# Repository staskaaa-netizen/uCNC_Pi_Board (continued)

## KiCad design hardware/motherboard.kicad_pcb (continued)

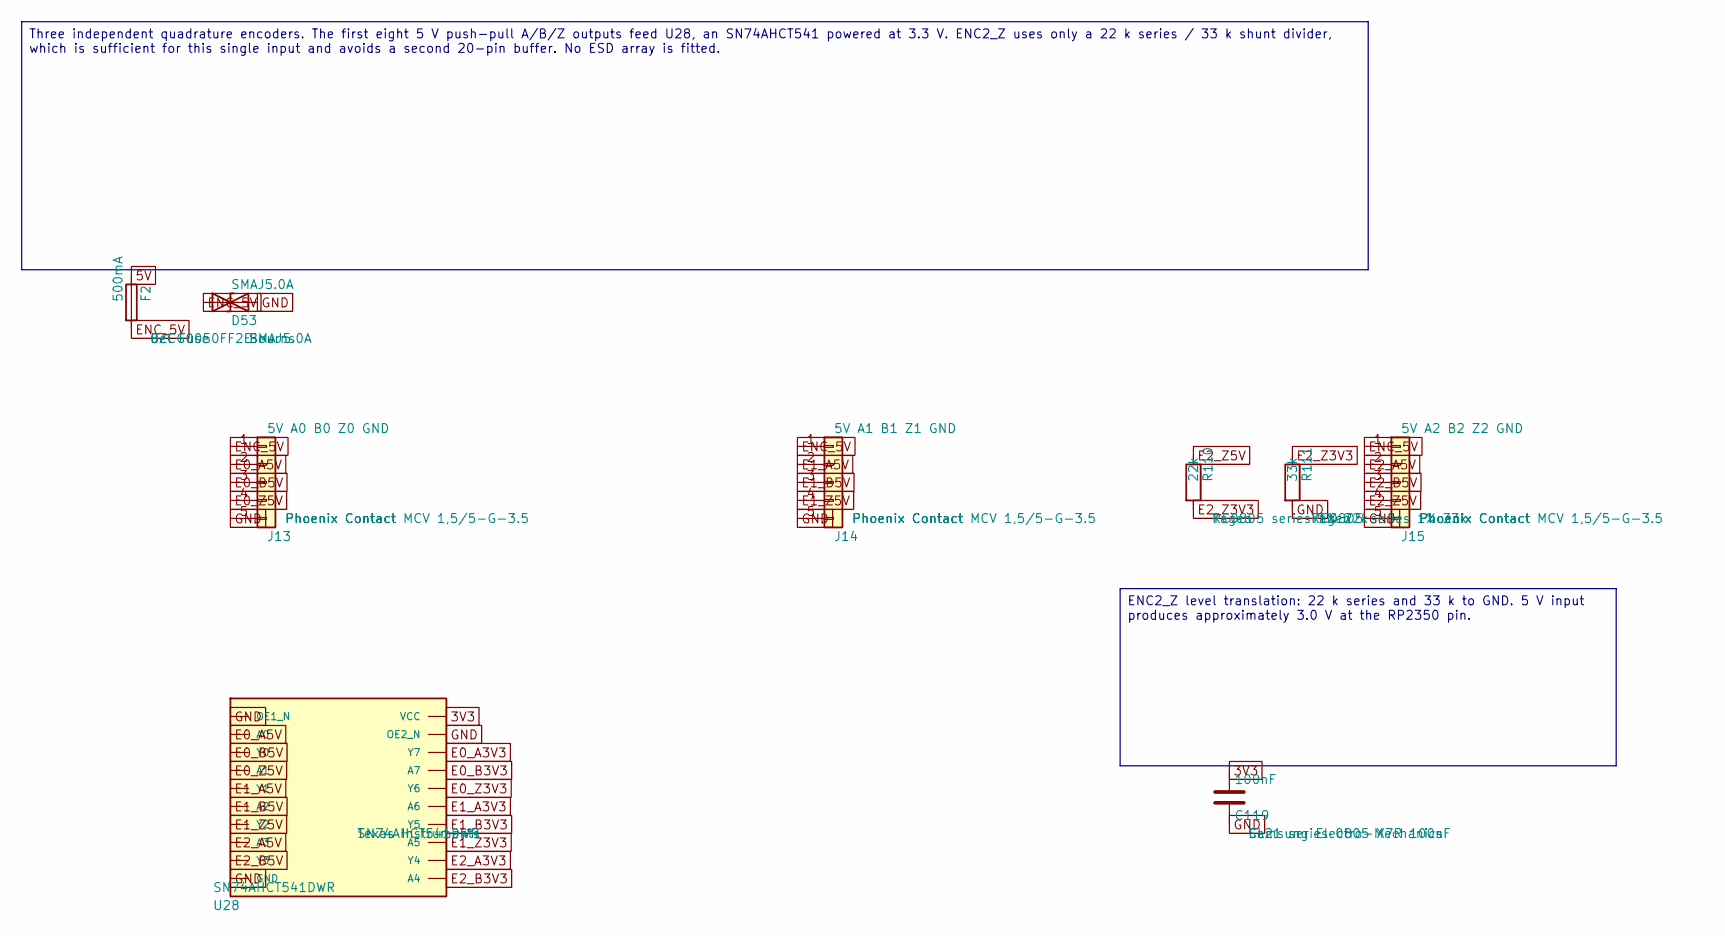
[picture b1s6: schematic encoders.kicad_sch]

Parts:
C119: 100nF; C_0805_2012Metric; MPN CL21 series 0805 X7R 100nF
D53: SMAJ5.0A; D_SMA; MPN SMAJ5.0A
F2: 500mA; R_1206_3216Metric; MPN 0ZCG0050FF2E
J13: 5V A0 B0 Z0 GND; PhoenixContact_MCV_1,5_5-G-3.5_1x05_P3.50mm_Vertical; MPN Phoenix Contact MCV 1,5/5-G-3.5
J14: 5V A1 B1 Z1 GND; PhoenixContact_MCV_1,5_5-G-3.5_1x05_P3.50mm_Vertical; MPN Phoenix Contact MCV 1,5/5-G-3.5
J15: 5V A2 B2 Z2 GND; PhoenixContact_MCV_1,5_5-G-3.5_1x05_P3.50mm_Vertical; MPN Phoenix Contact MCV 1,5/5-G-3.5
R110: 22k; R_0805_2012Metric; MPN RC0805 series 1% 22k
R111: 33k; R_0805_2012Metric; MPN RC0805 series 1% 33k
U28: SN74AHCT541DWR; SOIC-20W_7.5x12.8mm_P1.27mm; MPN SN74AHCT541DWR

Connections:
3V3: C119.1, U28.20 (VCC); also elsewhere on the board
5V: F2.1; also elsewhere on the board
E0_A3V3: U28.18 (Y7); also elsewhere on the board
E0_A5V: J13.2, U28.2 (A0)
E0_B3V3: U28.17 (A7); also elsewhere on the board
E0_B5V: J13.3, U28.3 (Y0)
E0_Z3V3: U28.16 (Y6); also elsewhere on the board
E0_Z5V: J13.4, U28.4 (A1)
E1_A3V3: U28.15 (A6); also elsewhere on the board
E1_A5V: J14.2, U28.5 (Y1)
E1_B3V3: U28.14 (Y5); also elsewhere on the board
E1_B5V: J14.3, U28.6 (A2)
E1_Z3V3: U28.13 (A5); also elsewhere on the board
E1_Z5V: J14.4, U28.7 (Y2)
E2_A3V3: U28.12 (Y4); also elsewhere on the board
E2_A5V: J15.2, U28.8 (A3)
E2_B3V3: U28.11 (A4); also elsewhere on the board
E2_B5V: J15.3, U28.9 (Y3)
E2_Z3V3: R110.2, R111.1; also elsewhere on the board
E2_Z5V: J15.4, R110.1
ENC_5V: D53.1 (A1), F2.2, J13.1, J14.1, J15.1
GND: C119.2, D53.2 (A2), J13.5, J14.5, J15.5, R111.2, U28.1 (OE1_N), U28.10 (GND), U28.19 (OE2_N); also elsewhere on the board

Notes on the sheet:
Three independent quadrature encoders. The first eight 5 V push-pull A/B/Z outputs feed U28, an SN74AHCT541 powered at 3.3 V. ENC2_Z uses only a 22 k series / 33 k shunt divider, which is sufficient for this single input and avoids a second 20-pin buffer. No ESD array is fitted.
ENC2_Z level translation: 22 k series and 33 k to GND. 5 V input produces approximately 3.0 V at the RP2350 pin.

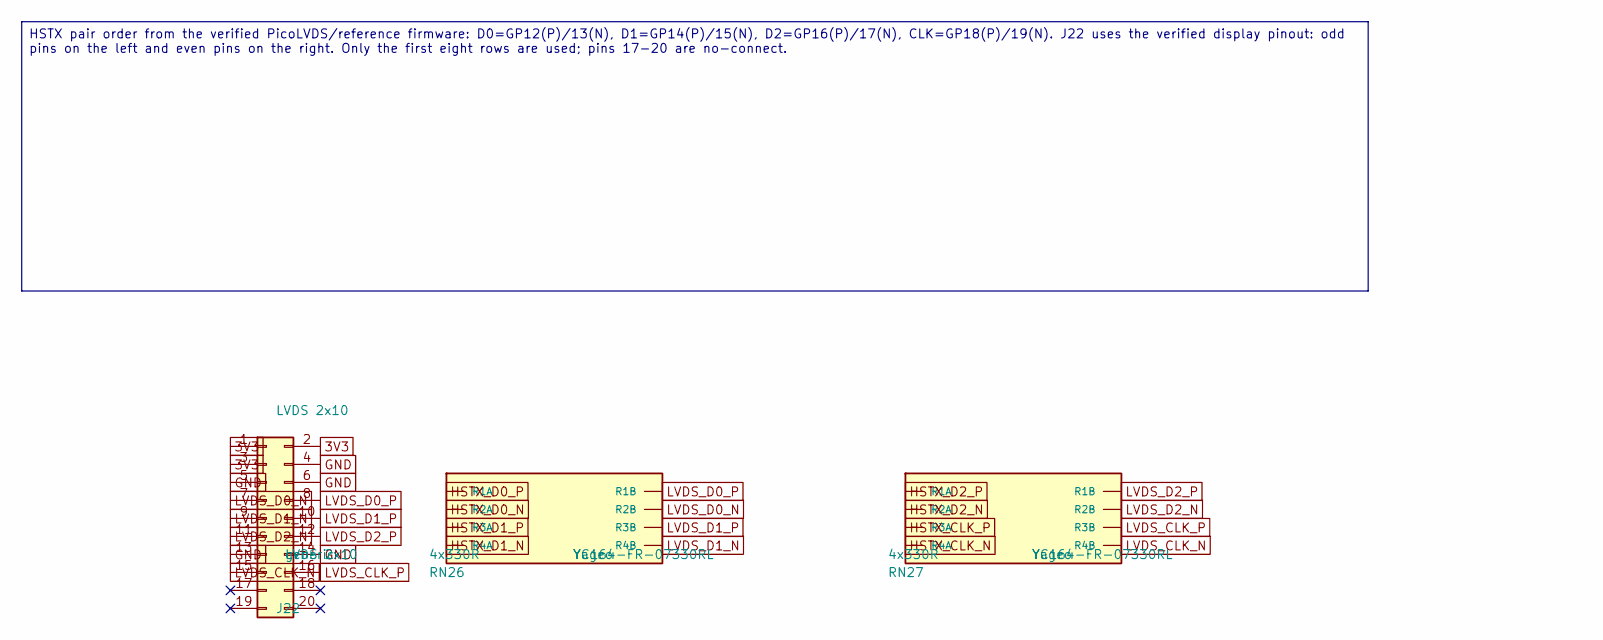
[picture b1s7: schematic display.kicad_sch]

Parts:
J22: LVDS 2x10; PinHeader_2x10_P2.00mm_Vertical; MPN LVDS 2x10
RN26, RN27: 4x330R; R_Array_Convex_4x0603; MPN YC164-FR-07330RL

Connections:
3V3: J22.1, J22.2, J22.3; also elsewhere on the board
GND: J22.4, J22.5, J22.6, J22.13, J22.14; also elsewhere on the board
HSTX_CLK_N: RN27.4 (R4A); also elsewhere on the board
HSTX_CLK_P: RN27.3 (R3A); also elsewhere on the board
HSTX_D0_N: RN26.2 (R2A); also elsewhere on the board
HSTX_D0_P: RN26.1 (R1A); also elsewhere on the board
HSTX_D1_N: RN26.4 (R4A); also elsewhere on the board
HSTX_D1_P: RN26.3 (R3A); also elsewhere on the board
HSTX_D2_N: RN27.2 (R2A); also elsewhere on the board
HSTX_D2_P: RN27.1 (R1A); also elsewhere on the board
LVDS_CLK_N: J22.15, RN27.5 (R4B)
LVDS_CLK_P: J22.16, RN27.6 (R3B)
LVDS_D0_N: J22.7, RN26.7 (R2B)
LVDS_D0_P: J22.8, RN26.8 (R1B)
LVDS_D1_N: J22.9, RN26.5 (R4B)
LVDS_D1_P: J22.10, RN26.6 (R3B)
LVDS_D2_N: J22.11, RN27.7 (R2B)
LVDS_D2_P: J22.12, RN27.8 (R1B)

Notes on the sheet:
HSTX pair order from the verified PicoLVDS/reference firmware: D0=GP12(P)/13(N), D1=GP14(P)/15(N), D2=GP16(P)/17(N), CLK=GP18(P)/19(N). J22 uses the verified display pinout: odd pins on the left and even pins on the right. Only the first eight rows are used; pins 17-20 are no-connect.

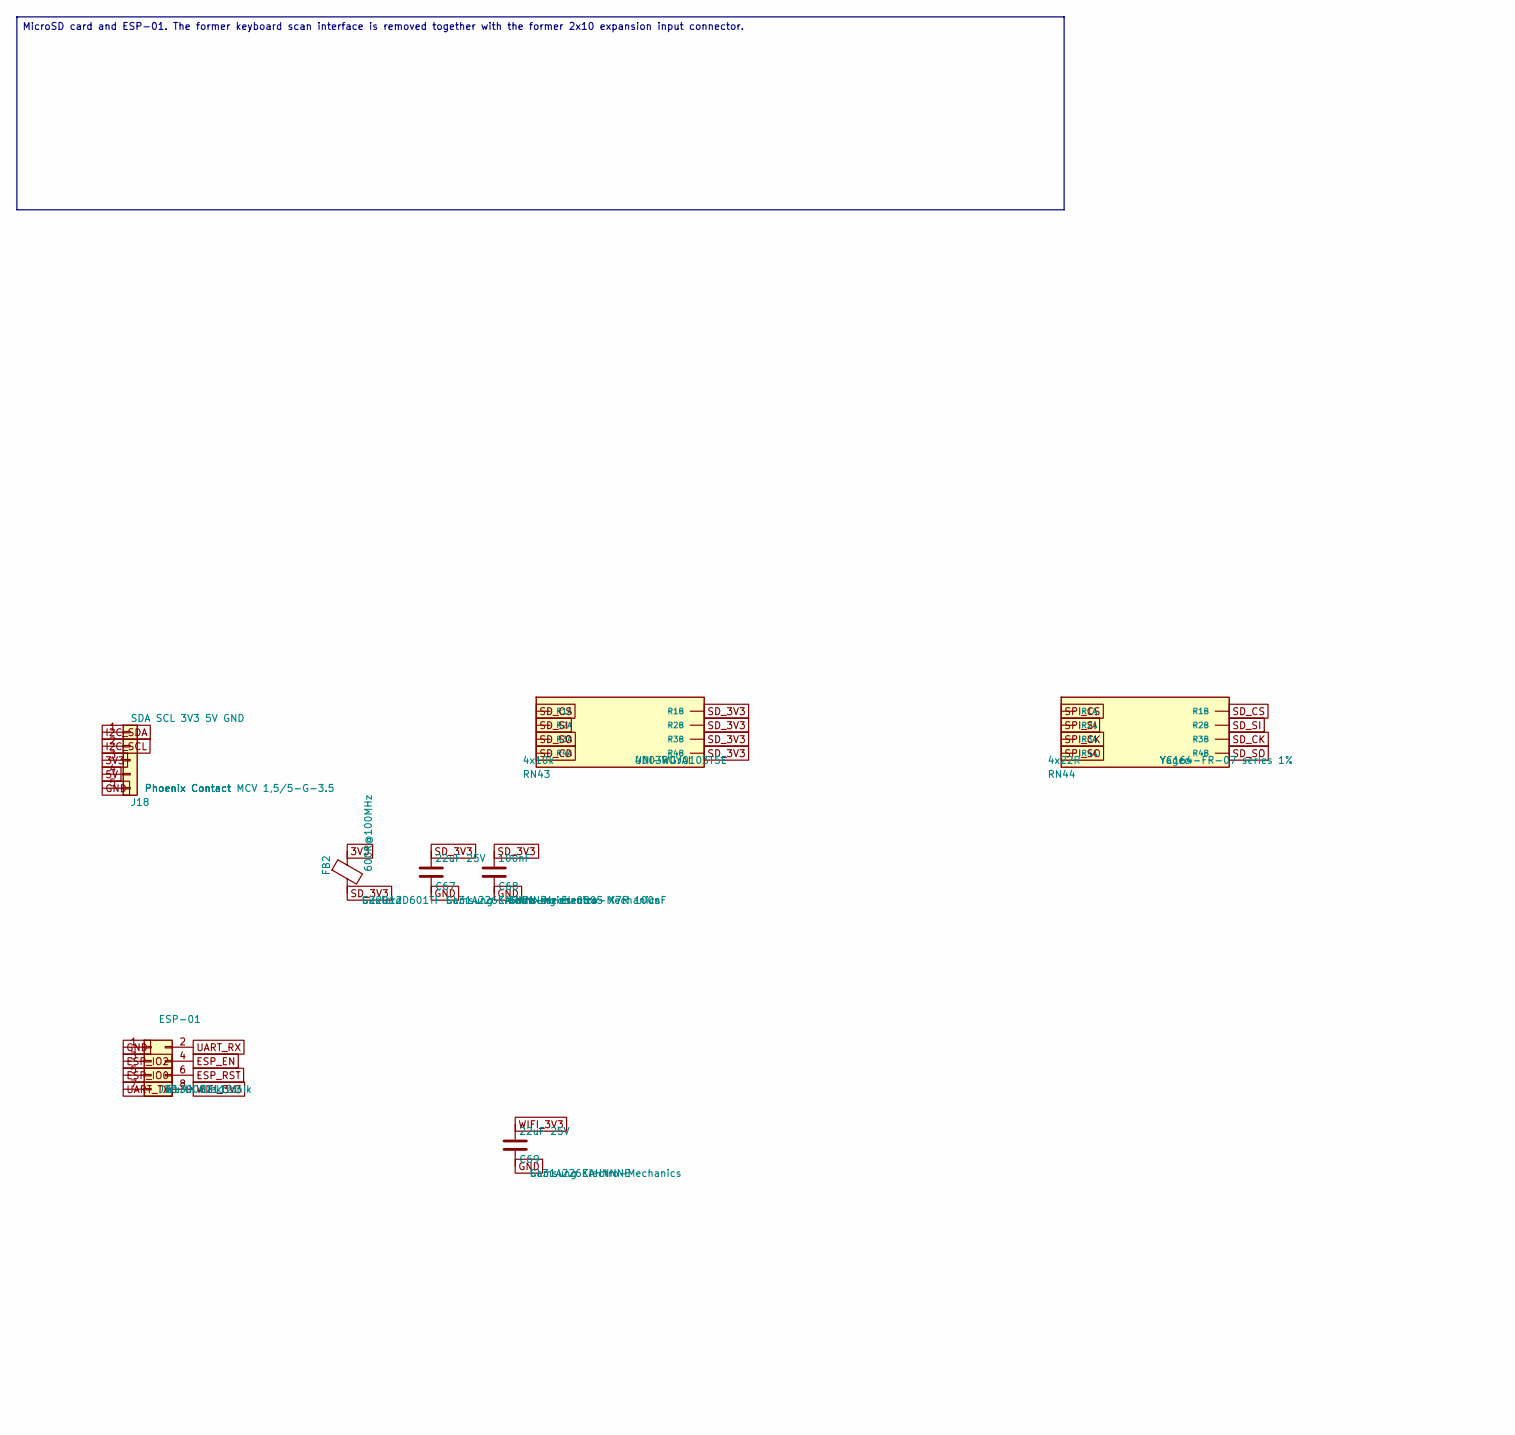
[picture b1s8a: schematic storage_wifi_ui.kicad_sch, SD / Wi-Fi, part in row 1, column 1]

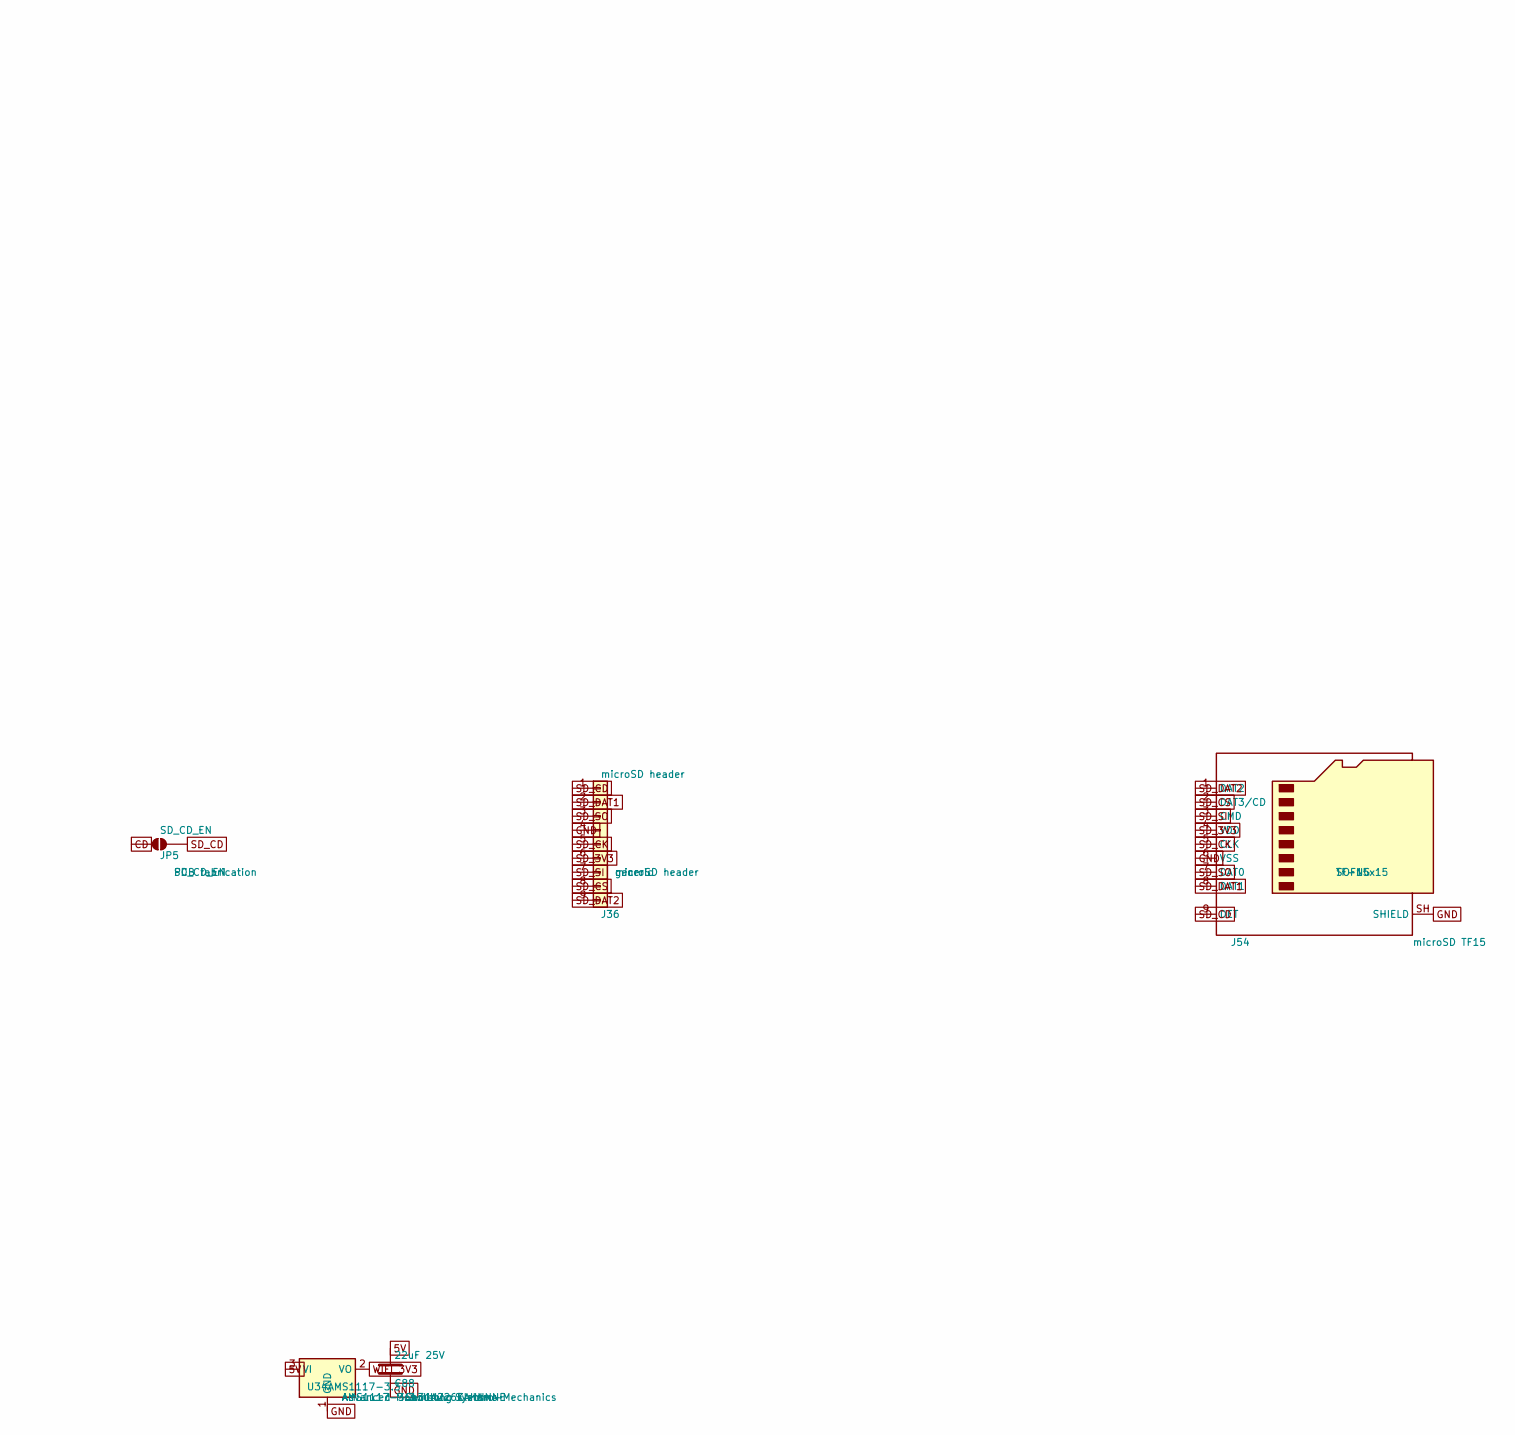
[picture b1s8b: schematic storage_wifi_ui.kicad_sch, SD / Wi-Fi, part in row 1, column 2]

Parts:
C67, C69, C88: 22uF 25V; C_1206_3216Metric; MPN CL31A226KAHNNNE
C68: 100nF; C_0805_2012Metric; MPN CL21 series 0805 X7R 100nF
FB2: 600R@100MHz; R_0805_2012Metric; MPN GZ2012D601TF
J18: SDA SCL 3V3 5V GND; PhoenixContact_MCV_1,5_5-G-3.5_1x05_P3.50mm_Vertical; MPN Phoenix Contact MCV 1,5/5-G-3.5
J20: ESP-01; PinSocket_2x04_P2.54mm_Vertical; MPN 61300821121
J36: microSD header; PinHeader_1x09_P2.54mm_Vertical; MPN microSD header
J54: microSD TF15; TF-SMD_TF-15-15; MPN TF-15x15
JP5: SD_CD_EN; SolderJumper-2_P1.3mm_Open_Pad1.0x1.5mm; MPN SD_CD_EN
RN43: 4x10k; R_Array_Convex_4x0603; MPN 4D03WGJ0103T5E
RN44: 4x22R; R_Array_Convex_4x0603; MPN YC164-FR-07 series 1%
U34: AMS1117-3.3; SOT-223-3_TabPin2; MPN AMS1117-3.3

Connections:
3V3: FB2.1, J18.3; also elsewhere on the board
5V: C88.1, J18.4, U34.3 (VI); also elsewhere on the board
CD: JP5.1 (A); also elsewhere on the board
ESP_EN: J20.4
ESP_IO0: J20.5
ESP_IO2: J20.3
ESP_RST: J20.6
GND: C67.2, C68.2, C69.2, C88.2, J18.5, J20.1, J36.4, J54.6 (VSS), J54.10, J54.11, J54.12, J54.13, J54.SH (SHIELD), U34.1 (GND); also elsewhere on the board
I2C_SCL: J18.2; also elsewhere on the board
I2C_SDA: J18.1; also elsewhere on the board
SD_3V3: C67.1, C68.1, FB2.2, J36.6, J54.4 (VDD), RN43.5 (R4B), RN43.6 (R3B), RN43.7 (R2B), RN43.8 (R1B)
SD_CD: J36.1, J54.9 (DET), JP5.2 (B), RN43.4 (R4A)
SD_CK: J36.5, J54.5 (CLK), RN44.6 (R3B)
SD_CS: J36.8, J54.2 (DAT3/CD), RN43.1 (R1A), RN44.8 (R1B)
SD_DAT1: J36.2, J54.8 (DAT1)
SD_DAT2: J36.9, J54.1 (DAT2)
SD_SI: J36.7, J54.3 (CMD), RN43.2 (R2A), RN44.7 (R2B)
SD_SO: J36.3, J54.7 (DAT0), RN43.3 (R3A), RN44.5 (R4B)
SPI_CK: RN44.3 (R3A); also elsewhere on the board
SPI_CS: RN44.1 (R1A); also elsewhere on the board
SPI_SI: RN44.2 (R2A); also elsewhere on the board
SPI_SO: RN44.4 (R4A); also elsewhere on the board
UART_RX: J20.2; also elsewhere on the board
UART_TX: J20.7; also elsewhere on the board
WIFI_3V3: C69.1, J20.8, U34.2 (VO)

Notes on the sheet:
MicroSD card and ESP-01. The former keyboard scan interface is removed together with the former 2x10 expansion input connector.

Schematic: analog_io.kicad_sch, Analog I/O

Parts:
C73, C74, C75, C93, C95, C97, C99, C102, C118: 100nF; C_0805_2012Metric; MPN CL21 series 0805 X7R 100nF
C92, C94, C96, C98: 1uF; C_0805_2012Metric; MPN CL21 series 0805 X7R 1uF
C100: 22uF 35V; C_1210_3225Metric; MPN CL32 series 1210 X7R 22uF 35V
C101: 22uF 25V; C_1206_3216Metric; MPN CL31A226KAHNNNE
J24: GND AI0 AI1 AI2 AI3; PhoenixContact_MCV_1,5_5-G-3.5_1x05_P3.50mm_Vertical; MPN Phoenix Contact MCV 1,5/5-G-3.5
J25: GND AO0 AO1 AO2 AO3; PhoenixContact_MCV_1,5_5-G-3.5_1x05_P3.50mm_Vertical; MPN Phoenix Contact MCV 1,5/5-G-3.5
R61, R64, R67, R182: 100k; R_0805_2012Metric; MPN RC0805 series 1% 100k
R63, R66, R69, R183: 33k; R_0805_2012Metric; MPN RC0805 series 1% 33k
R92, R93, R94, R95, R96, R97, R98, R99, R104, R105, R106, R107: 10k; R_0805_2012Metric; MPN RC0805 series 1% 10k
R100, R101, R102, R103: 22k; R_0805_2012Metric; MPN RC0805 series 1% 22k
U37: L78L12ACUTR; SOT-89-3_Handsoldering; MPN L78L12ACUTR
U38: TLV2374IDR; SOIC-14_3.9x8.7mm_P1.27mm; MPN TLV2374IDR

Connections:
ADC0: C73.1, R61.2, R63.1; also elsewhere on the board
ADC1: C74.1, R64.2, R66.1; also elsewhere on the board
ADC2: C75.1, R67.2, R69.1; also elsewhere on the board
ADC3: C118.1, R182.2, R183.1; also elsewhere on the board
AI0: J24.2, R61.1
AI1: J24.3, R64.1
AI2: J24.4, R67.1
AI3: J24.5, R182.1
AO0: J25.2, R100.2, U38.1 (1OUT)
AO0_1: C92.1, R92.2, R96.1
AO0_2: C93.1, R96.2, U38.3 (1IN_P)
AO0_FB: R100.1, R104.1, U38.2 (1IN_N)
AO1: J25.3, R101.2, U38.7 (2OUT)
AO1_1: C94.1, R93.2, R97.1
AO1_2: C95.1, R97.2, U38.5 (2IN_P)
AO1_FB: R101.1, R105.1, U38.6 (2IN_N)
AO2: J25.4, R102.2, U38.8 (3OUT)
AO2_1: C96.1, R94.2, R98.1
AO2_2: C97.1, R98.2, U38.10 (3IN_P)
AO2_FB: R102.1, R106.1, U38.9 (3IN_N)
AO3: J25.5, R103.2, U38.14 (4OUT)
AO3_1: C98.1, R95.2, R99.1
AO3_2: C99.1, R99.2, U38.12 (4IN_P)
AO3_FB: R103.1, R107.1, U38.13 (4IN_N)
AO_12V: C101.1, C102.1, U37.1 (OUT), U38.4 (VPLUS)
GND: C73.2, C74.2, C75.2, C92.2, C93.2, C94.2, C95.2, C96.2, C97.2, C98.2, C99.2, C100.2, C101.2, C102.2, C118.2, J24.1, J25.1, R63.2, R66.2, R69.2, R104.2, R105.2, R106.2, R107.2, R183.2, U37.2 (GND), U38.11 (VMINUS); also elsewhere on the board
PWM0: R92.1; also elsewhere on the board
PWM1: R93.1; also elsewhere on the board
PWM2: R94.1; also elsewhere on the board
PWM3: R95.1; also elsewhere on the board
VIN_P: C100.1, U37.3 (IN); also elsewhere on the board

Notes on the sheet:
Four 0-10 V ADC inputs use a 100 k over 33 k divider and one 100 nF ADC capacitor per channel. Place each divider/filter group at J24, not at the MCU. Four ground-referenced 0-10 V outputs use individual 0805 resistors for the approved two-stage 10 k / 1 uF and 10 k / 100 nF PWM filters. A TLV2374 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

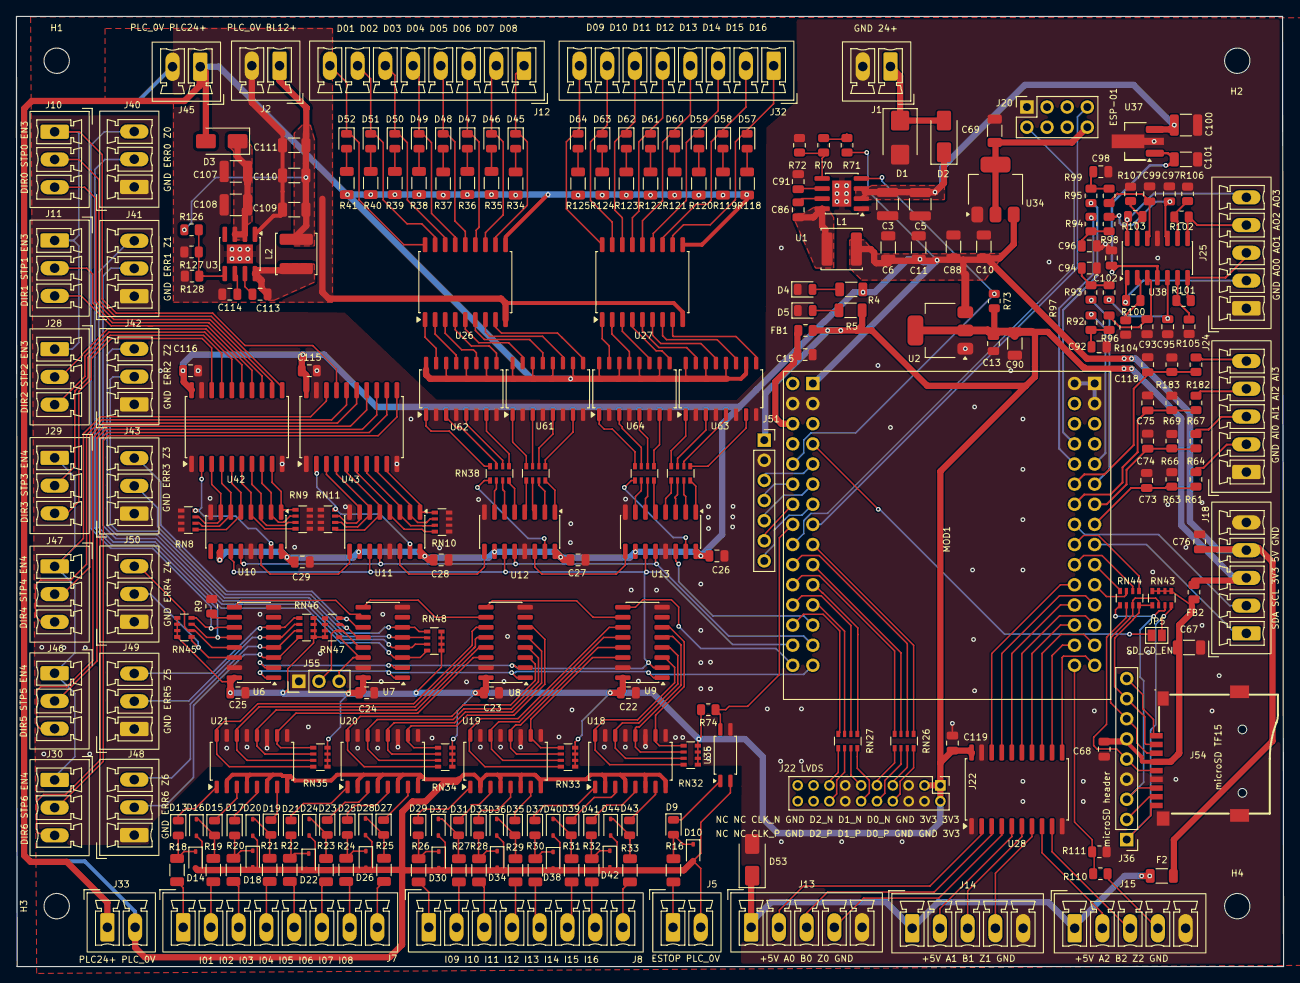
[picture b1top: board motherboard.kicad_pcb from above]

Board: 2 copper layers, 159.9 x 119.9 mm, 268 parts (0 on the bottom side), 317 nets.

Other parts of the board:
H1, H2, H3, H4: M3; MountingHole_3.2mm_M3

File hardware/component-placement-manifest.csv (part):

reference,value,sheet,functional_block,channels,role,associated_ic_or_net,placement_rule,current_status,side,x_mm,y_mm,dnp,nets
C3,22uF 35V,Power,Power,,bulk input capacitor,U1 input,place at regulator/load entry; preserve short power loop,inside,F.Cu,109.931,23.673,False,GND; VIN_P
C5,22uF 35V,Power,Power,,bulk input capacitor,U1 input,place at regulator/load entry; preserve short power loop,inside,F.Cu,114.046,23.698,False,GND; VIN_P
C6,22uF 25V,Power,Power,,bulk output capacitor,U1 output,place at regulator/load entry; preserve short power loop,inside,F.Cu,110.007,29.159,False,5V; GND
C10,22uF 25V,Power,Power,,bulk input capacitor,U2 input,place at regulator/load entry; preserve short power loop,inside,F.Cu,122.072,29.058,False,5V; GND
C11,22uF 25V,Power,Power,,bulk output capacitor,U1 output,place at regulator/load entry; preserve short power loop,inside,F.Cu,114.021,29.159,False,5V; GND
C13,100nF,Power,Power,,decoupling capacitor,U2 output,place immediately beside associated IC supply and GND pins; minimize loop,inside,F.Cu,123.286,41.279,False,3V3; GND
C15,100nF,Power,Power,,decoupling capacitor,ADC_3V3 filter,place immediately beside associated IC supply and GND pins; minimize loop,inside,F.Cu,99.06,42.672,False,ADC_3V3; GND
C76,100nF,Power,Power,,decoupling capacitor,U2 input,place immediately beside associated IC supply and GND pins; minimize loop,inside,F.Cu,149.301,66.294,False,5V; GND
C86,100nF,Power,Power,,bootstrap capacitor,U1 BOOT to SW,place directly between regulator BOOT and SW pins,inside,F.Cu,98.648,24.403,False,B5_BST; B5_SW
C90,22uF 25V,Power,Power,,bulk output capacitor,U2 output,place at regulator/load entry; preserve short power loop,inside,F.Cu,125.984,41.279,False,3V3; GND
C91,1uF,Power,Power,,IC VCC bypass capacitor,U1 VCC,place immediately beside associated IC supply and GND pins; minimize loop,inside,F.Cu,98.648,20.847,False,B5_VCC; GND
C107,22uF 35V,Power,Power,,bulk input capacitor,U3 input,place at regulator/load entry; preserve short power loop,inside,F.Cu,27.686,19.558,False,BL_VIN; PLC_0V
C108,22uF 35V,Power,Power,,decoupling capacitor,U3 input,place immediately beside associated IC supply and GND pins; minimize loop,inside,F.Cu,27.686,23.774,False,BL_VIN; PLC_0V
C109,22uF 25V,Power,Power,,bulk output capacitor,U3 output,place at regulator/load entry; preserve short power loop,inside,F.Cu,35.052,24.384,False,BL_12V; PLC_0V
C110,22uF 25V,Power,Power,,bulk output capacitor,U3 output,place at regulator/load entry; preserve short power loop,inside,F.Cu,35.052,20.066,False,BL_12V; PLC_0V
C111,22uF 25V,Power,Power,,bulk output capacitor,U3 output,place at regulator/load entry; preserve short power loop,inside,F.Cu,35.052,16.256,False,BL_12V; PLC_0V
C113,100nF,Power,Power,,bootstrap capacitor,U3 BOOT to SW,place directly between regulator BOOT and SW pins,inside,F.Cu,30.734,35.052,False,B12_BST; B12_SW
C114,1uF,Power,Power,,IC VCC bypass capacitor,U3 VCC,place immediately beside associated IC supply and GND pins; minimize loop,inside,F.Cu,26.924,35.052,False,B12_VCC; PLC_0V
D1,SMBJ24CA,Power,Power,,diode,protection/clamp/rectification,place in functional block; keep GND return short,inside,F.Cu,111.506,15.291,False,GND; VIN
D2,US1M,Power,Power,,diode,protection/clamp/rectification,place with functional block; review after placement,inside,F.Cu,117.043,15.138,False,VIN; VIN_P
D3,US1M,Power,Power,,diode,protection/clamp/rectification,place with functional block; review after placement,inside,F.Cu,25.908,15.748,False,BL_VIN; PLC_24V
D4,5V LED,Power,Power,,LED,indicator/protection,place in functional block; keep GND return short,inside,F.Cu,99.517,34.442,False,GND; P5V_LED
D5,3V3 LED,Power,Power,,LED,indicator/protection,place in functional block; keep GND return short,inside,F.Cu,99.54,37.109,False,GND; P3V3_LED
FB1,600R@100MHz,Power,Power,,ferrite bead,rail filtering,place with functional block; review after placement,inside,F.Cu,99.568,39.624,False,3V3; ADC_3V3
J1,24+ GND,Power,main power connector,,connector,external or board-level connection,mechanical anchor; do not move without approval,inside,F.Cu,110.292,6.317,False,GND; VIN
J2,BL12+ PLC_0V,Power,backlight/CCFL connector,,connector,external or board-level connection,mechanical anchor; do not move without approval,inside,F.Cu,33.2,6.215,False,BL_12V; PLC_0V
L1,22uH 1.4A,Power,Power,,inductor,switching power stage,place with functional block; review after placement,inside,F.Cu,104.14,29.352,False,5V; B5_SW
L2,47uH 0.9A,Power,Power,,inductor,switching power stage,place with functional block; review after placement,inside,F.Cu,35.306,29.972,False,B12_SW; BL_12V
R4,2.2k,Power,Power,,pull-up resistor,digital state definition,place with functional block; review after placement,inside,F.Cu,105.342,34.442,False,5V; P5V_LED
R5,2.2k,Power,Power,,pull-up resistor,digital state definition,place with functional block; review after placement,inside,F.Cu,105.255,37.084,False,3V3; P3V3_LED
R70,33k,Power,Power,,pull-up resistor,digital state definition,place with functional block; review after placement,inside,F.Cu,104.806,16.256,False,5V; FB5_T
R71,100k,Power,Power,,resistor,series/divider/limit passive,place with functional block; review after placement,inside,F.Cu,101.854,16.256,False,FB5; FB5_T
R72,33k,Power,Power,,resistor,series/divider/limit passive,place in functional block; keep GND return short,inside,F.Cu,98.806,16.256,False,FB5; GND
R73,100k,Power,Power,,pull-up resistor,digital state definition,place with functional block; review after placement,inside,F.Cu,123.393,35.916,False,3V3; PG_N
R126,100k,Power,Power,,pull-up resistor,digital state definition,place with functional block; review after placement,inside,F.Cu,22.098,26.924,False,BL_12V; FB12
R127,10k,Power,Power,,resistor,series/divider/limit passive,place with functional block; review after placement,inside,F.Cu,22.098,29.718,False,FB12; PLC_0V
R128,100k,Power,Power,,resistor,series/divider/limit passive,place with functional block; review after placement,inside,F.Cu,22.16,32.766,False,FB12; PLC_0V
U1,LMR36510ADDAR,Power,Power,,IC,active device,place in functional block; keep GND return short,inside,F.Cu,104.14,22.352,False,B5_BST; B5_SW; B5_VCC; FB5; GND; PG_N; VIN_P
U2,AMS1117-3.3,Power,Power,,IC,active device,place in functional block; keep GND return short,inside,F.Cu,116.586,39.624,False,3V3; 5V; GND
U3,LMR36510ADDAR,Power,Power,,IC,active device,place with functional block; review after placement,inside,F.Cu,28.194,29.972,False,B12_BST; B12_SW; B12_VCC; BL_VIN; FB12; PLC_0V
C22,100nF,MCU / SHIFT,MCU / SHIFT,,decoupling capacitor,U6,place immediately beside associated IC supply and GND pins; minimize loop,inside,F.Cu,77.216,85.344,False,3V3; GND
C23,100nF,MCU / SHIFT,MCU / SHIFT,,decoupling capacitor,U7,place immediately beside associated IC supply and GND pins; minimize loop,inside,F.Cu,59.944,85.344,False,3V3; GND
C24,100nF,MCU / SHIFT,MCU / SHIFT,,decoupling capacitor,U8,place immediately beside associated IC supply and GND pins; minimize loop,inside,F.Cu,44.196,85.344,False,3V3; GND
C25,100nF,MCU / SHIFT,MCU / SHIFT,,decoupling capacitor,U9,place immediately beside associated IC supply and GND pins; minimize loop,inside,F.Cu,27.94,85.344,False,3V3; GND
C26,100nF,MCU / SHIFT,MCU / SHIFT,,decoupling capacitor,U13,place immediately beside associated IC supply and GND pins; minimize loop,inside,F.Cu,88.392,68.072,False,5V; GND
C27,100nF,MCU / SHIFT,MCU / SHIFT,,decoupling capacitor,U12,place immediately beside associated IC supply and GND pins; minimize loop,inside,F.Cu,70.866,68.58,False,5V; GND
C28,100nF,MCU / SHIFT,MCU / SHIFT,,decoupling capacitor,U11,place immediately beside associated IC supply and GND pins; minimize loop,inside,F.Cu,53.594,68.58,False,5V; GND
C29,100nF,MCU / SHIFT,MCU / SHIFT,,decoupling capacitor,U10,place immediately beside associated IC supply and GND pins; minimize loop,inside,F.Cu,36.068,68.834,False,5V; GND
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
